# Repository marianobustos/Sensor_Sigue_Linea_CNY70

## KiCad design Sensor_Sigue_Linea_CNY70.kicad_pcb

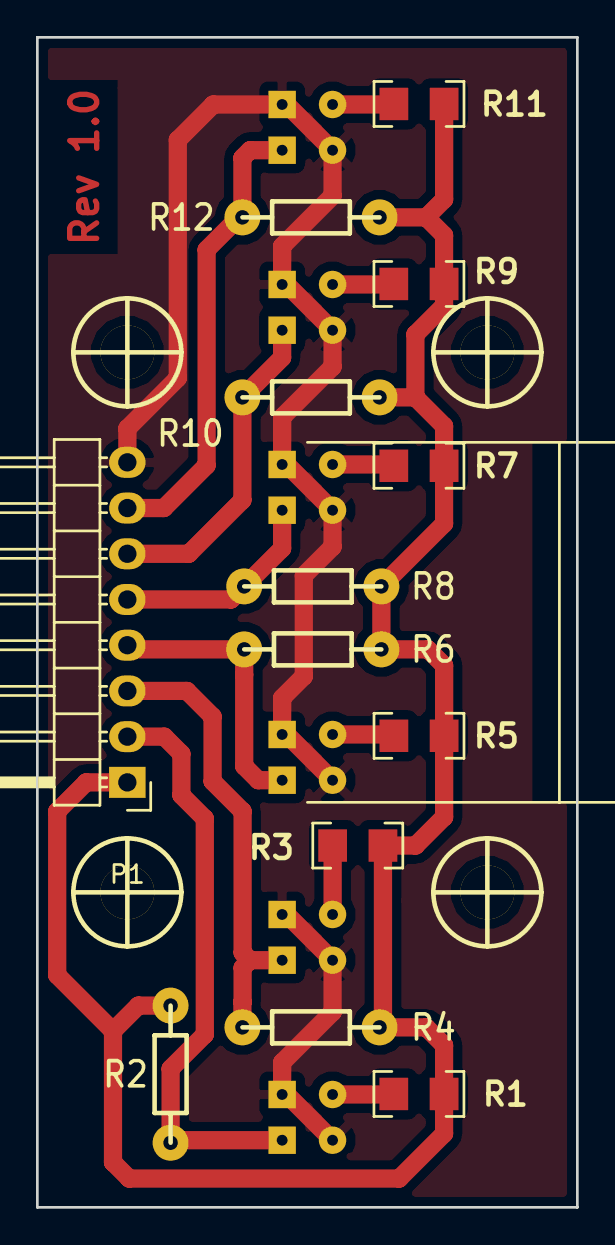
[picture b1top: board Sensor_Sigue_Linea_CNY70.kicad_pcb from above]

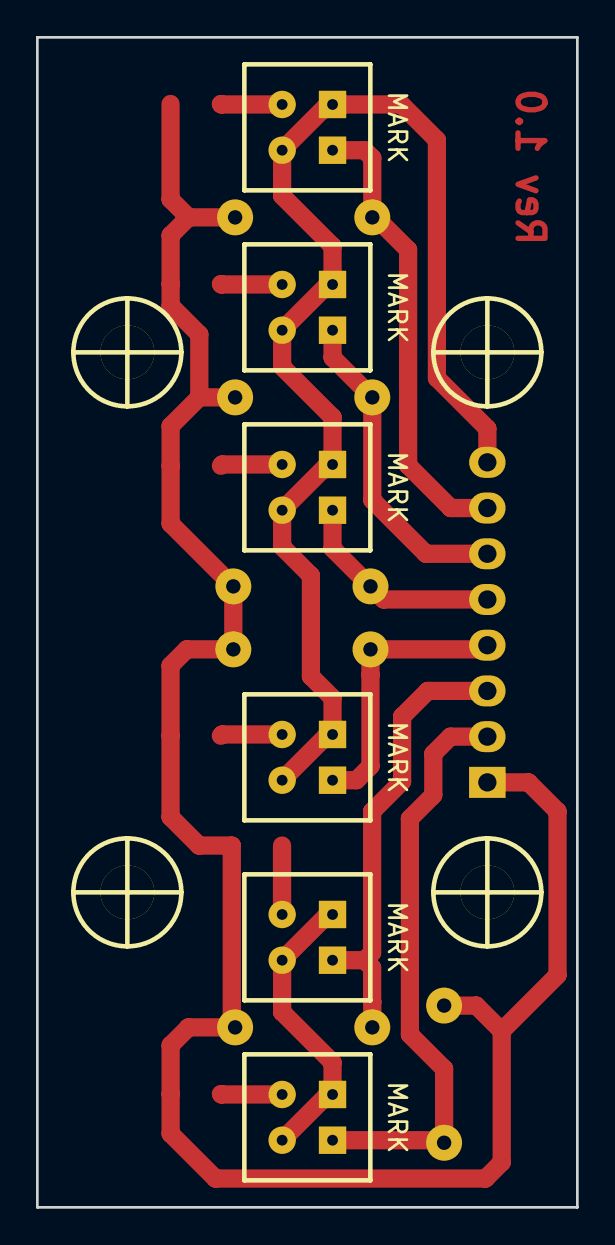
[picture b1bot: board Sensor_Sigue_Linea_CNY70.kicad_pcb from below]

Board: 2 copper layers, 30.0 x 65.0 mm, 24 parts (6 on the bottom side), 14 nets.

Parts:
H1, H2, H3, H4: Mounting_Hole; hole_3mm
P0: Pista; Pista_Velocista
P1: CONN_01X08; Pin_Header_Angled_1x08
R1, R3, R5, R7, R9, R11: 100; R_1206
R2, R4, R6, R8, R10, R12: 4K7; RES0.3
U1, U2, U3, U4, U5, U6: CNY70

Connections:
/A0: P1.2, R2.1, U1.3
/A1: P1.3, R4.1, U2.3
/A2: P1.4, R6.1, U3.3
/A3: P1.5, R8.1, U4.3
/A4: P1.6, R10.1, U5.3
/A5: P1.7, R12.1, U6.3
GND: P1.8, U1.2, U1.4, U2.2, U2.4, U3.2, U3.4, U4.2, U4.4, U5.2, U5.4, U6.2, U6.4
unnamed: R1.2, U1.1
unnamed: R3.2, U2.1
unnamed: R5.2, U3.1
unnamed: R7.2, U4.1
unnamed: R9.2, U5.1
unnamed: R11.2, U6.1
VDD: P1.1, R1.1, R2.2, R3.1, R4.2, R5.1, R6.2, R7.1, R8.2, R9.1, R10.2, R11.1, R12.2

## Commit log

2017-11-22 Versión inicial
